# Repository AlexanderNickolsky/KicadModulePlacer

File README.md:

# KicadModulePlacer

## What is KicadModulePlacer

This is a Kicad PCB editor plugin that helps to place modules at pre-computed coordinates.

## Who may need it

I am using it to place LEDs on boards. Any project that comprises many similar components, like LEDs, logic gates, diodes, resistors, etc.
arranged in a systematic order may benefit from this plugin.

## How to use it

1. Install the plugin as usual. See https://dev-docs.kicad.org/en/python/pcbnew/

2. Create a file in your favorite spreadsheet program (Libre Office, Microsoft Office, whatever)

3. Calculate coordinates for modules. You need at least three colums: module name, X coordinate, Y coordinate.
You may want to add the third one for rotation. Select the range with coordinates, copy and paste it into a plain text
file. coord.txt is a good name for it.

4. Start the plugin in the Kicad PCB editor using Tools - External Plugins - Module Placer. File selection dialog will appear.
Open your coord.txt file.

5. That's it. You may want to close the file and reopen it for ratsnests to be re-created.

There is an example project in the ModulePlacerTesting folder.

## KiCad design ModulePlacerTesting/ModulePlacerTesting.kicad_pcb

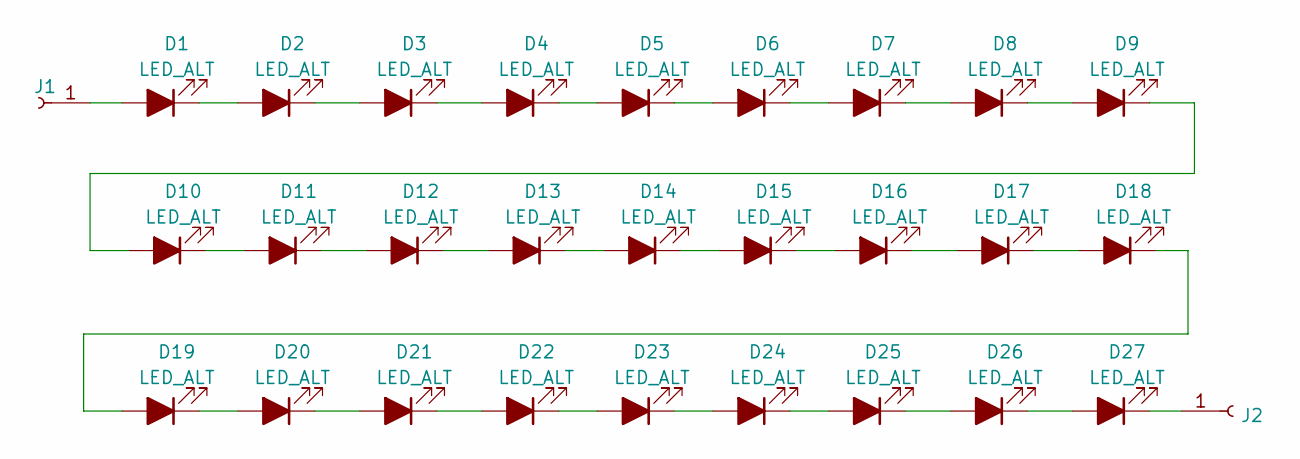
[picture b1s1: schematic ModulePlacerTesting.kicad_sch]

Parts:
D1, D2, D3, D4, D5, D6, D7, D8, D9, D10, D11, D12, D13, D14, D15, D16, D17, D18, D19, D20, D21, D22, D23, D24, D25, D26, D27: LED_ALT; LED_PLCC_2835_Handsoldering
J1, J2: Conn_01x01_Female; PinHeader_1x01_P2.54mm_Vertical

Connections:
unnamed: D1.1 (K), D2.2 (A)
unnamed: D1.2 (A), J1.1
unnamed: D2.1 (K), D3.2 (A)
unnamed: D3.1 (K), D4.2 (A)
unnamed: D4.1 (K), D5.2 (A)
unnamed: D5.1 (K), D6.2 (A)
unnamed: D6.1 (K), D7.2 (A)
unnamed: D7.1 (K), D8.2 (A)
unnamed: D8.1 (K), D9.2 (A)
unnamed: D10.1 (K), D11.2 (A)
unnamed: D9.1 (K), D10.2 (A)
unnamed: D11.1 (K), D12.2 (A)
unnamed: D12.1 (K), D13.2 (A)
unnamed: D13.1 (K), D14.2 (A)
unnamed: D14.1 (K), D15.2 (A)
unnamed: D15.1 (K), D16.2 (A)
unnamed: D16.1 (K), D17.2 (A)
unnamed: D17.1 (K), D18.2 (A)
unnamed: D18.1 (K), D19.2 (A)
unnamed: D19.1 (K), D20.2 (A)
unnamed: D20.1 (K), D21.2 (A)
unnamed: D21.1 (K), D22.2 (A)
unnamed: D22.1 (K), D23.2 (A)
unnamed: D23.1 (K), D24.2 (A)
unnamed: D24.1 (K), D25.2 (A)
unnamed: D25.1 (K), D26.2 (A)
unnamed: D26.1 (K), D27.2 (A)
unnamed: D27.1 (K), J2.1

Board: 2 copper layers, 29 parts (0 on the bottom side), 28 nets, no tracks yet.

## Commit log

2022-12-06 Update ModulePlacer.py
    Added ratsnest recalculation
2023-11-27 Add files via upload
    KiCad 7 compatibility
